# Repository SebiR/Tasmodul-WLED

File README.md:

# Tasmodul WLED
A module for WLED or Tasmota to drive WS281x LED strips

## Features
* 3 push buttons (customizable function)
* Infrared receiver for standard remote controls
* Integrated level shifter for 5/12V strips

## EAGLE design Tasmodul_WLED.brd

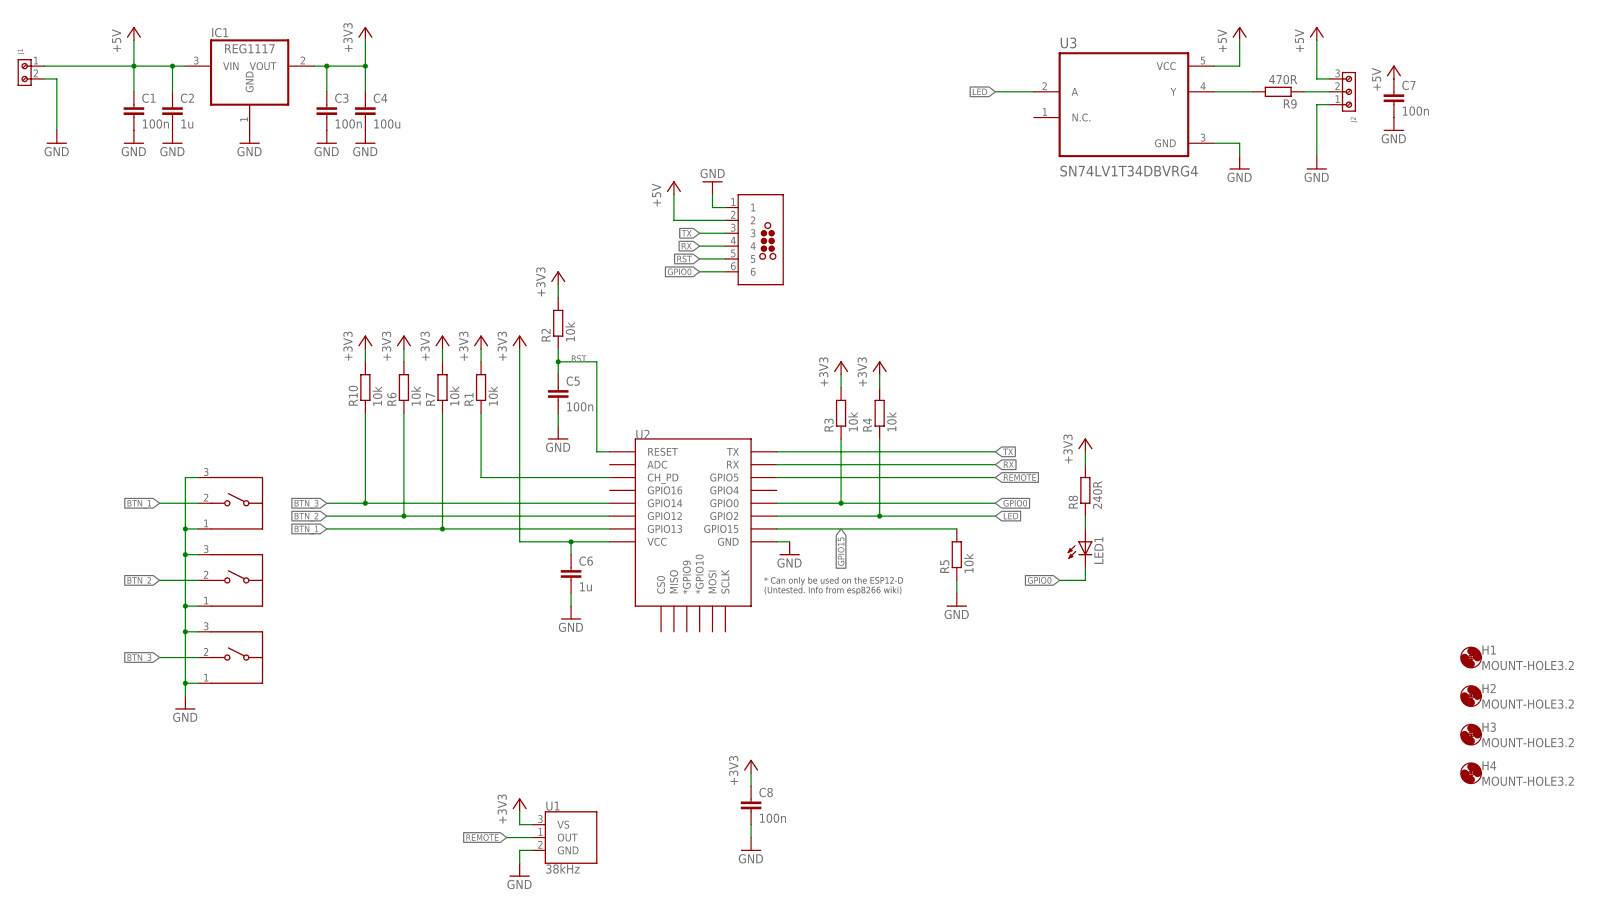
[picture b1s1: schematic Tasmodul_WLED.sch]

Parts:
C1, C3, C5, C7, C8: 100n; C0603
C2, C6: 1u; C0603
C4: 100u; C0603
H1, H2, H3, H4: MOUNT-HOLE3.2; 3,2
IC1: REG1117; SOT223
J1: 691210910002
J2: 691210910003
J6: TC2030-MCP-NL
LED1: LEDCHIP-LED0603; CHIP-LED0603
R1, R2, R3, R4, R5, R6, R7, R10: 10k; R0603
R8: 240R; R0603
R9: 470R; R0603
S1, S2, S3: 436333033816
U1: 38kHz; TSOP382
U2: ESP12ESMD; ESP12E-SMD
U3: SN74LV1T34DBVRG4; SOT95P280X145-5N

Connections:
+3V3: C3.1, C4.1, C6.1, C8.1, IC1.2 (VOUT), R1.2, R2.2, R3.2, R4.2, R6.2, R7.2, R8.2, R10.2, U1.3 (VS), U2.VCC
+5V: C1.1, C2.1, C7.1, IC1.3 (VIN), J1.1, J2.3, J6.2, U3.5 (VCC)
BTN_1: R7.1, S3.2, U2.GPIO13
BTN_2: R6.1, S2.2, U2.GPIO12
BTN_3: R10.1, S1.2, U2.GPIO14
GND: C1.2, C2.2, C3.2, C4.2, C5.2, C6.2, C7.2, C8.2, IC1.1 (GND), J1.2, J2.1, J6.1, R5.1, S1.1, S1.3, S2.1, S2.3, S3.1, S3.3, U1.2 (GND), U2.GND, U3.3 (GND)
GPIO0: J6.6, LED1.C, R3.1, U2.GPIO0
GPIO15: R5.2, U2.GPIO15
LED: R4.1, U2.GPIO2, U3.2 (A)
unnamed: LED1.A, R8.1
unnamed: R9.2, U3.4 (Y)
unnamed: J2.2, R9.1
unnamed: R1.1, U2.CH_PD
REMOTE: U1.1 (OUT), U2.GPIO5
RST: C5.1, J6.5, R2.1, U2.RESET
RX: J6.4, U2.RXD0 (RX)
TX: J6.3, U2.TXD0 (TX)

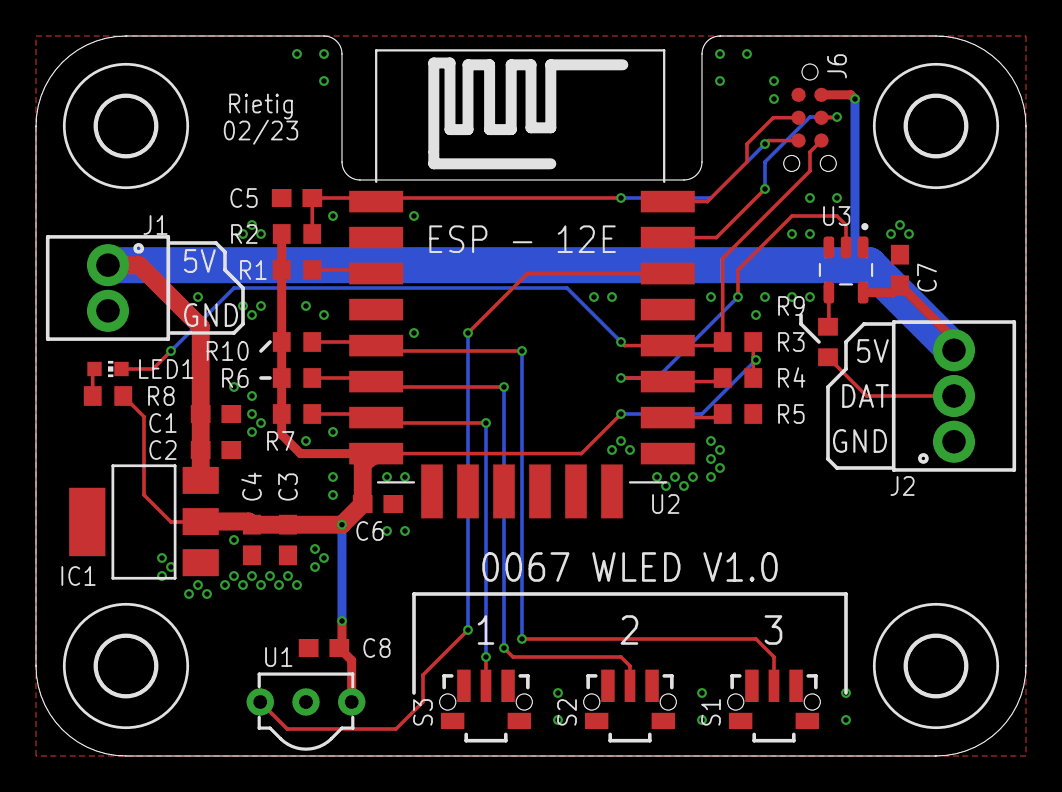
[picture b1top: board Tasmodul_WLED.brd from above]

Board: 2 copper layers, 55.0 x 40.0 mm, 33 parts (0 on the bottom side), 17 nets.

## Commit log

2023-08-05 Added .gitignore to versioned files

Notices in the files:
parts and their libraries:
Wurth_Switch_WS-TASU: Copyright: Würth Elektronik
SparkFun-Sensors: Licensing: Creative Commons ShareAlike 4.0 International - https://creativecommons.org/licenses/by-sa/4.0
tag-connect: ©2009 ROFA.cz - modified and updated by Robert Darlington ‹rdarlington@gmail.com›
